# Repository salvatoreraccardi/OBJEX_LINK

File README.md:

# OBJEX Link 

**OBJEX Link website:** https://objex.link/

**OBJEX Link Docs:** https://docs.objex.link/

**email:** info@objex.link 

**OBJEX Link Shop:** https://www.tindie.com/stores/objex/

**Youtube:** <br />
Project introduction - **OBJEX Link** [watch the video](https://www.youtube.com/watch?v=X29LyX-1ozA)

Assembly and testing - **Protoboard&Socket_v2.0** [watch the video](https://www.youtube.com/watch?v=N7MFNUX0_PA)

Assembly and testing - **OBJEX Link v1.6-C3:** [watch the video](https://www.youtube.com/watch?v=o9e5-9o4egI)

Assembly and testing - **OBJEX Link v1.6:** [watch the video](https://www.youtube.com/watch?v=haHsvLIlmms)

Assembly and testing - **OBJEX Link v1.5:** [watch the video](https://www.youtube.com/watch?v=wx3dR2j1C28)

Assembly and testing - **OBJEX Link v1.0:** [watch the video](https://www.youtube.com/watch?v=_4CofqktS38)

## What is OBJEX Link?
OBJEX Link is a modular IoT board. It is designed to develop **IoT devices** that are **easy to repair** and **recycle**. OBJEX Link is designed to meet a wide range of uses: **Smart Home & Cities, IIOT, Everyday things & Wearables, Predictive Maintenance, Agriculture Automation.**

OBJEX Link can also be used for **rapid prototyping, and developing research and robotics projects, with the right module you can extend the possible uses of the board.**

The compact form factor and board design ensure easy use and maintenance of the board. The architecture of OBJEX Link is composed of two parts, the first is the mainboard (OBJEX Link) and the second is the module allows for easy customization and interfacing with hardware compared to other IoT boards.

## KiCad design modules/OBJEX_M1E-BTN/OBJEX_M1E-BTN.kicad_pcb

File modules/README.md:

# OBJEX Modules
Modules are an essential element of OBJEX Link. In fact, they are the modules that allow OBJEX Link to detect the temperature, control an motor etc - *(like Arduino shields but smaller and more compact)*.

**Here are some features/components you can add with modules:**
- Sensors
- Relay 
- Motor driver(Stepper Motor, DC, LRA, ERM).
- OLED Display
- Convert slimstack connectors to larger connectors (type 2.54mm pitch connectors).
- A specific circuit (such as LoRa Module, PSRAM, PWM controller, etc).

## Types of modules
There are several form formats to ensure maximum customization.

| Type | Description     | Size    | PCB thickness | Connector | Connector Type | 3V3 | 5V | A |
|------|-----------------|---------|---------------|-----------|----------------|-----|----|---|
| M0   | Standard Module | 10x20mm | 0.8mm         | 2         |  BM28B0              |  ✓   |  ✓  | 5 |
| M1   | Standard Module | 20x20mm | 0.8mm         | 4         |  BM28B0              |  ✓   |  ✓  | 5 |
| M1E   | With I2C EEPROM | 20x20mm | 0.8mm         | 4         |  BM28B0              |  ✓   |  ✓  | 5 |

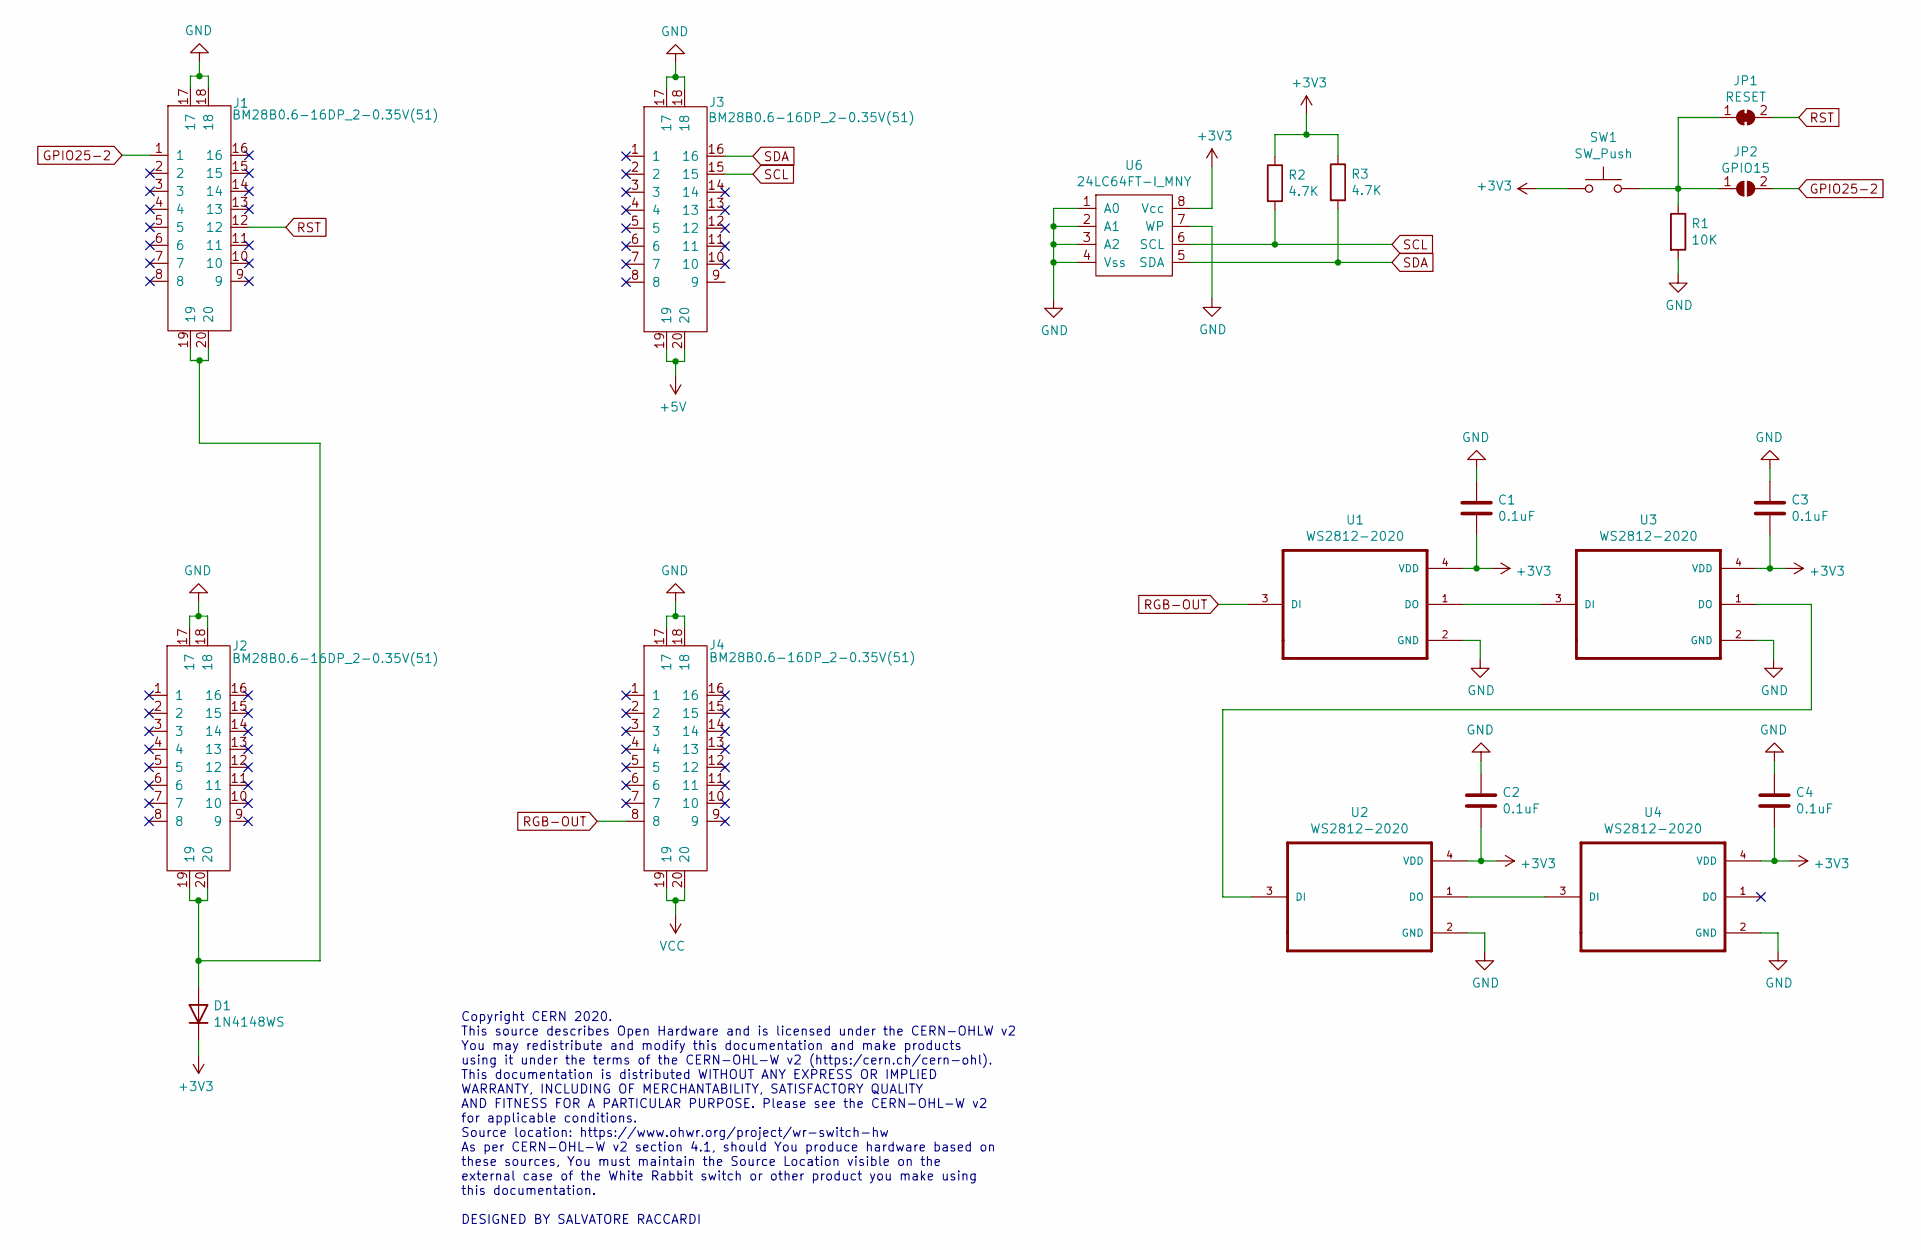
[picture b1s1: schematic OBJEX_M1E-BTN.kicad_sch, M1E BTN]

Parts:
C1, C2, C3, C4: 0.1uF; C_0402_1005Metric
D1: 1N4148WS; D_SOD-323
J1, J2, J3, J4: BM28B0.6-16DP_2-0.35V(51); BM28B0.6-16DP-2-0.35V(51)
JP1: RESET; SolderJumper-2_P1.3mm_Bridged_Pad1.0x1.5mm
JP2: GPIO15; SolderJumper-2_P1.3mm_Open_Pad1.0x1.5mm
R1: 10K; R_0402_1005Metric
R2, R3: 4.7K; R_0402_1005Metric
SW1: SW_Push; SW_Push_1P1T_NO_CK_PTS125Sx43PSMTR
U1, U2, U3, U4: WS2812-2020; LED_WS2812-2020
U6: 24LC64FT-I_MNY; SON50P200X300X80-8N

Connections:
+3V3: C1.2, C2.2, C3.2, C4.2, D1.1 (K), R2.1, R3.1, SW1.1, U1.4 (VDD), U2.4 (VDD), U3.4 (VDD), U4.4 (VDD), U6.8 (Vcc)
+5V: J3.19, J3.20
GND: C1.1, C2.1, C3.1, C4.1, J1.17, J1.18, J2.17, J2.18, J3.17, J3.18, J4.17, J4.18, R1.2, U1.2 (GND), U2.2 (GND), U3.2 (GND), U4.2 (GND), U6.1 (A0), U6.2 (A1), U6.3 (A2), U6.4 (Vss), U6.7 (WP)
GPIO25-2: J1.1, JP2.2 (B); also elsewhere on the board
unnamed: D1.2 (A), J1.19, J1.20, J2.19, J2.20
unnamed 64: JP1.1 (A), JP2.1 (A), R1.1, SW1.2; also elsewhere on the board
unnamed: U1.1 (DO), U3.3 (DI)
unnamed: U2.1 (DO), U4.3 (DI)
unnamed: U2.3 (DI), U3.1 (DO)
RGB-OUT: J4.8, U1.3 (DI)
RST: J1.12, JP1.2 (B); also elsewhere on the board
SCL: J3.15, R2.2, U6.6 (SCL)
SDA: J3.16, R3.2, U6.5 (SDA)
VCC: J4.19, J4.20

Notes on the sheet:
Copyright CERN 2020. This source describes Open Hardware and is licensed under the CERN-OHLW v2 You may redistribute and modify this documentation and make products using it under the terms of the CERN-OHL-W v2 (https:/cern.ch/cern-ohl). This documentation is distributed WITHOUT ANY EXPRESS OR IMPL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

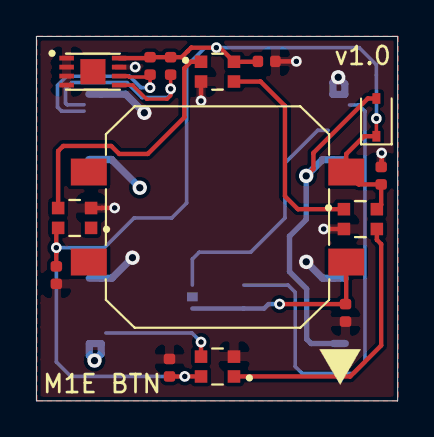
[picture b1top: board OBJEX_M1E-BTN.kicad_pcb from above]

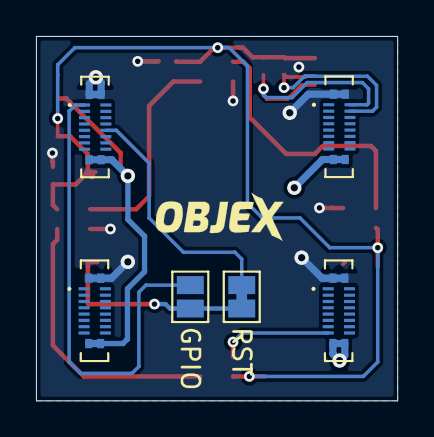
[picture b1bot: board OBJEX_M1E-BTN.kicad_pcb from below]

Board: 2 copper layers, 20.1 x 20.2 mm, 20 parts (6 on the bottom side), 14 nets.

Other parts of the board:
GPIO: GPIO15; SolderJumper-2_P1.3mm_Open_Pad1.0x1.5mm
RST: RESET; SolderJumper-2_P1.3mm_Bridged_Pad1.0x1.5mm

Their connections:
GPIO25-2: GPIO.2; also elsewhere on the board
unnamed 64: GPIO.1, RST.1; also elsewhere on the board
RST: RST.2; also elsewhere on the board

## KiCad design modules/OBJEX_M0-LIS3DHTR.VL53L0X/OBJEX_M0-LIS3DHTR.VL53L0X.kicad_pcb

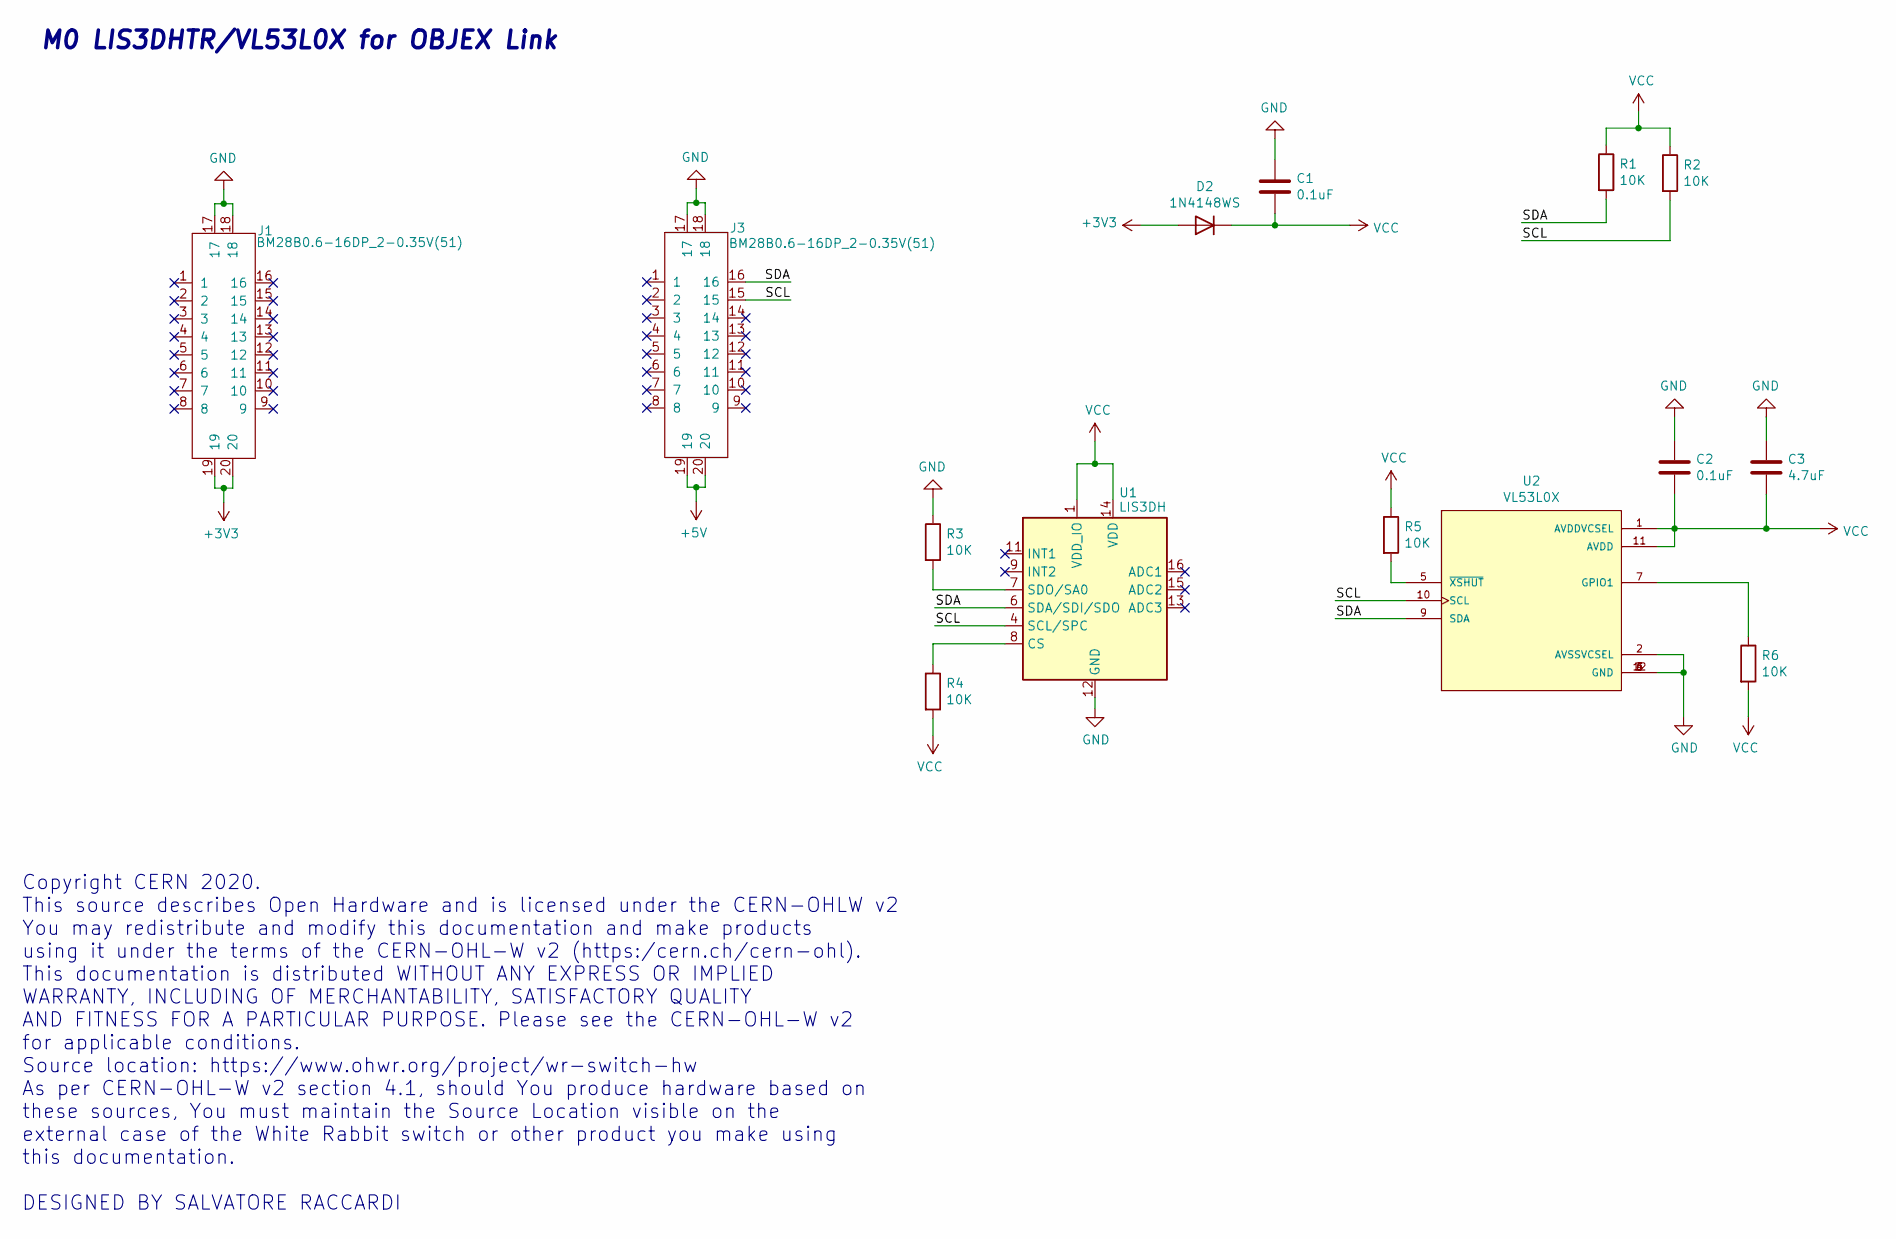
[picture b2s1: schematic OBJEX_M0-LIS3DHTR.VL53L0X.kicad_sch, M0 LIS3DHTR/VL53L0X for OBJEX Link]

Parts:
C1, C2: 0.1uF; C_0402_1005Metric
C3: 4.7uF; C_0402_1005Metric
D2: 1N4148WS; D_SOD-323
J1, J3: BM28B0.6-16DP_2-0.35V(51); BM28B0.6-16DP-2-0.35V(51)
R1, R2, R3, R4, R5, R6: 10K; R_0402_1005Metric
U1: LIS3DH; LGA-16_3x3mm_P0.5mm_LayoutBorder3x5y
U2: VL53L0X; SENSOR_VL53L0X; PART_REV 1.0

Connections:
+3V3: D2.2 (A), J1.19, J1.20
+5V: J3.19, J3.20
/SCL: J3.15, R2.2, U1.4 (SCL/SPC), U2.10 (SCL)
/SDA: J3.16, R1.2, U1.6 (SDA/SDI/SDO), U2.9 (SDA)
GND: C1.1, C2.1, C3.1, J1.17, J1.18, J3.17, J3.18, R3.1, U1.5 (GND), U1.10 (GND), U1.12 (GND), U2.2 (AVSSVCSEL), U2.3 (GND), U2.4 (GND), U2.6 (GND), U2.12 (GND)
unnamed: R3.2, U1.7 (SDO/SA0)
unnamed: R4.1, U1.8 (CS)
unnamed: R5.2, U2.5 (~XSHUT)
unnamed: R6.1, U2.7 (GPIO1)
VCC: C1.2, C2.2, C3.2, D2.1 (K), R1.1, R2.1, R4.2, R5.1, R6.2, U1.1 (VDD_IO), U1.14 (VDD), U2.1 (AVDDVCSEL), U2.11 (AVDD)

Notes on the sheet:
Copyright CERN 2020. This source describes Open Hardware and is licensed under the CERN-OHLW v2 You may redistribute and modify this documentation and make products using it under the terms of the CERN-OHL-W v2 (https:/cern.ch/cern-ohl). This documentation is distributed WITHOUT ANY EXPRESS OR IMPL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
M0 LIS3DHTR/VL53L0X for OBJEX Link

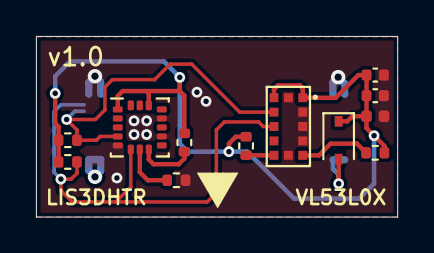
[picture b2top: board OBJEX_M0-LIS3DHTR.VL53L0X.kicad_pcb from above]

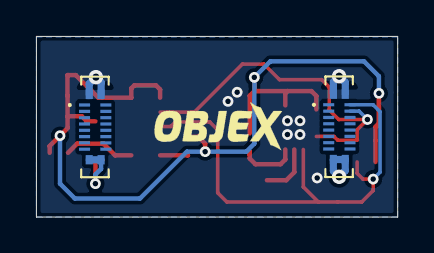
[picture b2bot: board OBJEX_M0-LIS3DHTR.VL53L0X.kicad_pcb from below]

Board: 2 copper layers, 20.1 x 10.0 mm, 14 parts (2 on the bottom side), 10 nets.

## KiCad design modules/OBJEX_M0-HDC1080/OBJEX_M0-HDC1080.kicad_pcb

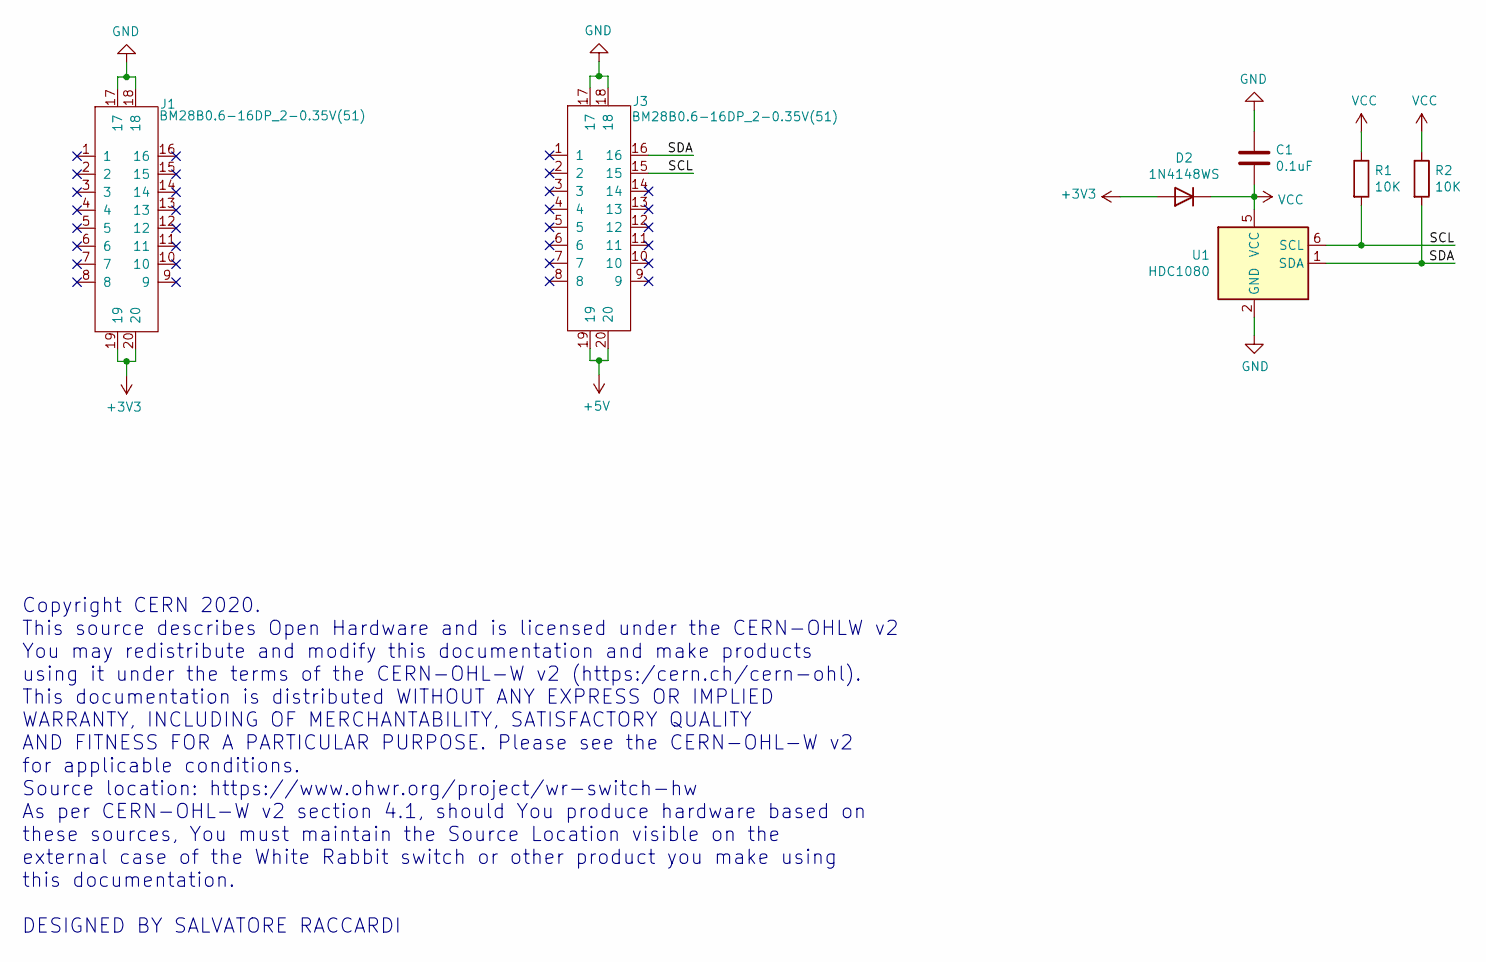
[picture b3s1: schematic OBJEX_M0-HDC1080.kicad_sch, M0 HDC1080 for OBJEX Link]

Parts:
C1: 0.1uF; C_0402_1005Metric
D2: 1N4148WS; D_SOD-323
J1, J3: BM28B0.6-16DP_2-0.35V(51); BM28B0.6-16DP-2-0.35V(51)
R1, R2: 10K; R_0603_1608Metric
U1: HDC1080; Texas_PWSON-N6

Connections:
+3V3: D2.2 (A), J1.19, J1.20
+5V: J3.19, J3.20
/SCL: J3.15, R1.2, U1.6 (SCL)
/SDA: J3.16, R2.2, U1.1 (SDA)
GND: C1.1, J1.17, J1.18, J3.17, J3.18, U1.2 (GND)
VCC: C1.2, D2.1 (K), R1.1, R2.1, U1.5 (VCC)

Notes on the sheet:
Copyright CERN 2020. This source describes Open Hardware and is licensed under the CERN-OHLW v2 You may redistribute and modify this documentation and make products using it under the terms of the CERN-OHL-W v2 (https:/cern.ch/cern-ohl). This documentation is distributed WITHOUT ANY EXPRESS OR IMPL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

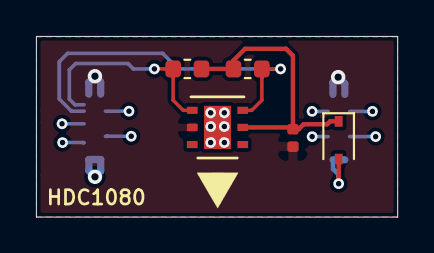
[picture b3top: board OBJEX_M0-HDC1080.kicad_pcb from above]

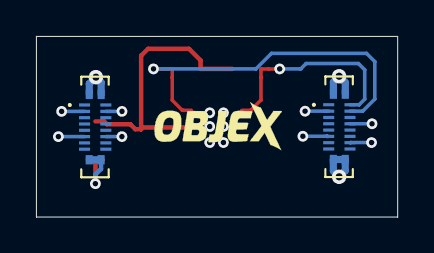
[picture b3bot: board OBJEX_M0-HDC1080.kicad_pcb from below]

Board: 2 copper layers, 20.1 x 10.0 mm, 7 parts (2 on the bottom side), 6 nets.

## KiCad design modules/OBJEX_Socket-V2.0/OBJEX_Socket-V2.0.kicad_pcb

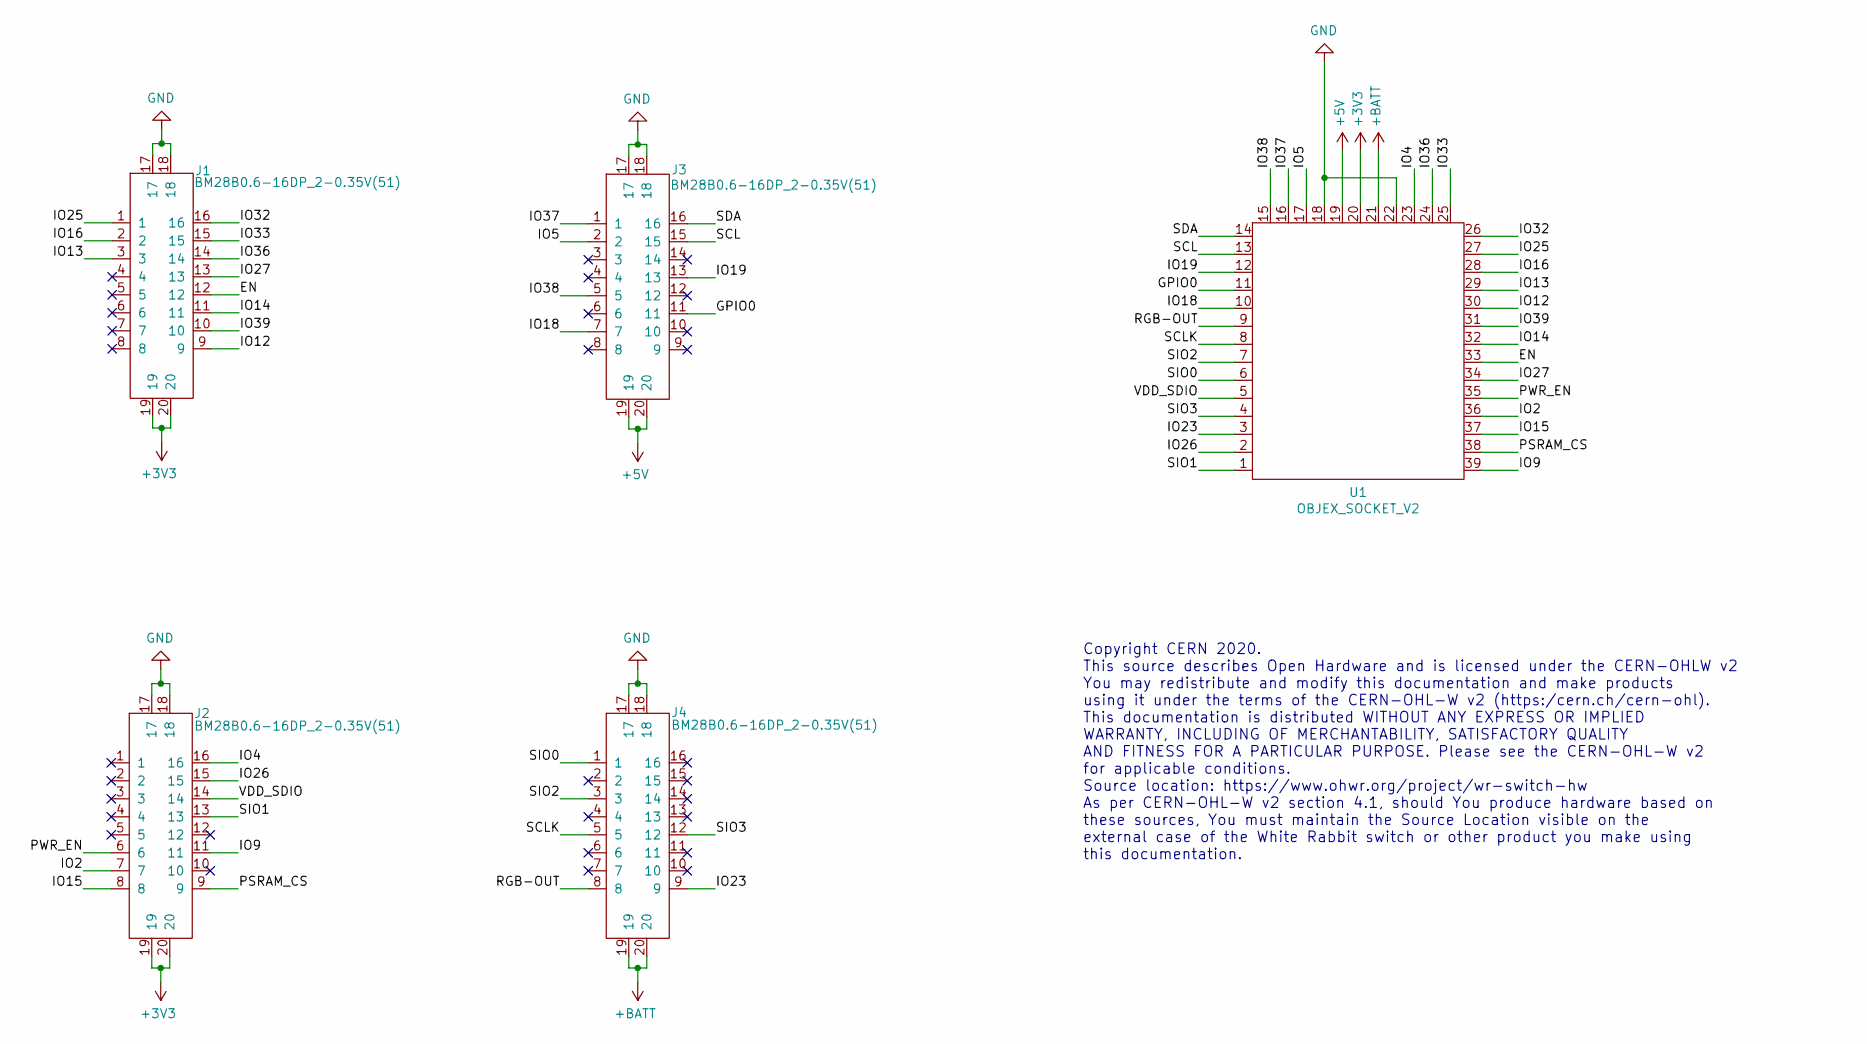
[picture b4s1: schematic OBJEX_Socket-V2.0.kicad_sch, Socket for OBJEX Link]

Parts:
J1, J2, J3, J4: BM28B0.6-16DP_2-0.35V(51); BM28B0.6-16DP-2-0.35V(51)
U1: OBJEX_SOCKET_V2; OBJEX_Link-Castellated

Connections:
+3V3: J1.19, J1.20, J2.19, J2.20, U1.20
+5V: J3.19, J3.20, U1.19
+BATT: J4.19, J4.20, U1.21
/EN: J1.12, U1.33
/GPIO0: J3.11, U1.11
/IO2: J2.7, U1.36
/IO4: J2.16, U1.23
/IO5: J3.2, U1.17
/IO9: J2.11, U1.39
/IO12: J1.9, U1.30
/IO13: J1.3, U1.29
/IO14: J1.11, U1.32
/IO15: J2.8, U1.37
/IO16: J1.2, U1.28
/IO18: J3.7, U1.10
/IO19: J3.13, U1.12
/IO23: J4.9, U1.3
/IO25: J1.1, U1.27
/IO26: J2.15, U1.2
/IO27: J1.13, U1.34
/IO32: J1.16, U1.26
/IO33: J1.15, U1.25
/IO36: J1.14, U1.24
/IO37: J3.1, U1.16
/IO38: J3.5, U1.15
/IO39: J1.10, U1.31
/PSRAM_CS: J2.9, U1.38
/PWR_EN: J2.6, U1.35
/RGB-OUT: J4.8, U1.9
/SCL: J3.15, U1.13
/SCLK: J4.5, U1.8
/SDA: J3.16, U1.14
/SIO0: J4.1, U1.6
/SIO1: J2.13, U1.1
/SIO2: J4.3, U1.7
/SIO3: J4.12, U1.4
/VDD_SDIO: J2.14, U1.5
GND: J1.17, J1.18, J2.17, J2.18, J3.17, J3.18, J4.17, J4.18, U1.18, U1.22

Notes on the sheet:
Copyright CERN 2020. This source describes Open Hardware and is licensed under the CERN-OHLW v2 You may redistribute and modify this documentation and make products using it under the terms of the CERN-OHL-W v2 (https:/cern.ch/cern-ohl). This documentation is distributed WITHOUT ANY EXPRESS OR IMPL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

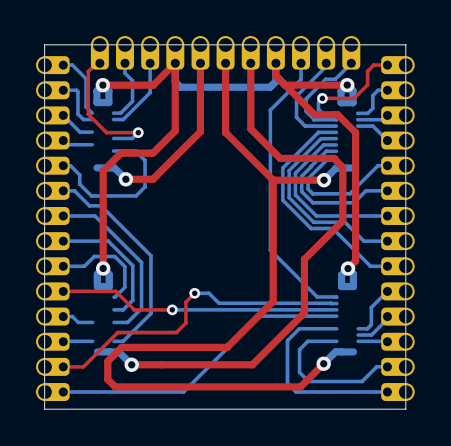
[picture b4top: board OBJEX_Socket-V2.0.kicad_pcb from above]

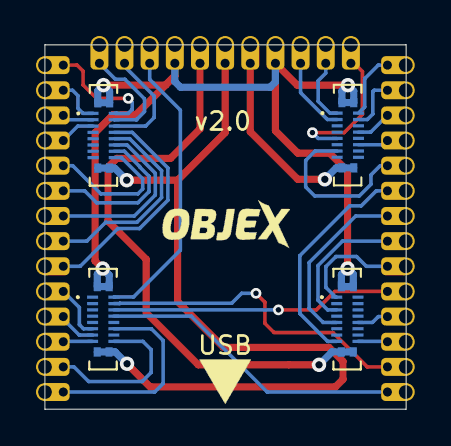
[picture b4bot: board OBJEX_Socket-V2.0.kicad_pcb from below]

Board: 2 copper layers, 20.1 x 20.2 mm, 5 parts (4 on the bottom side), 38 nets.

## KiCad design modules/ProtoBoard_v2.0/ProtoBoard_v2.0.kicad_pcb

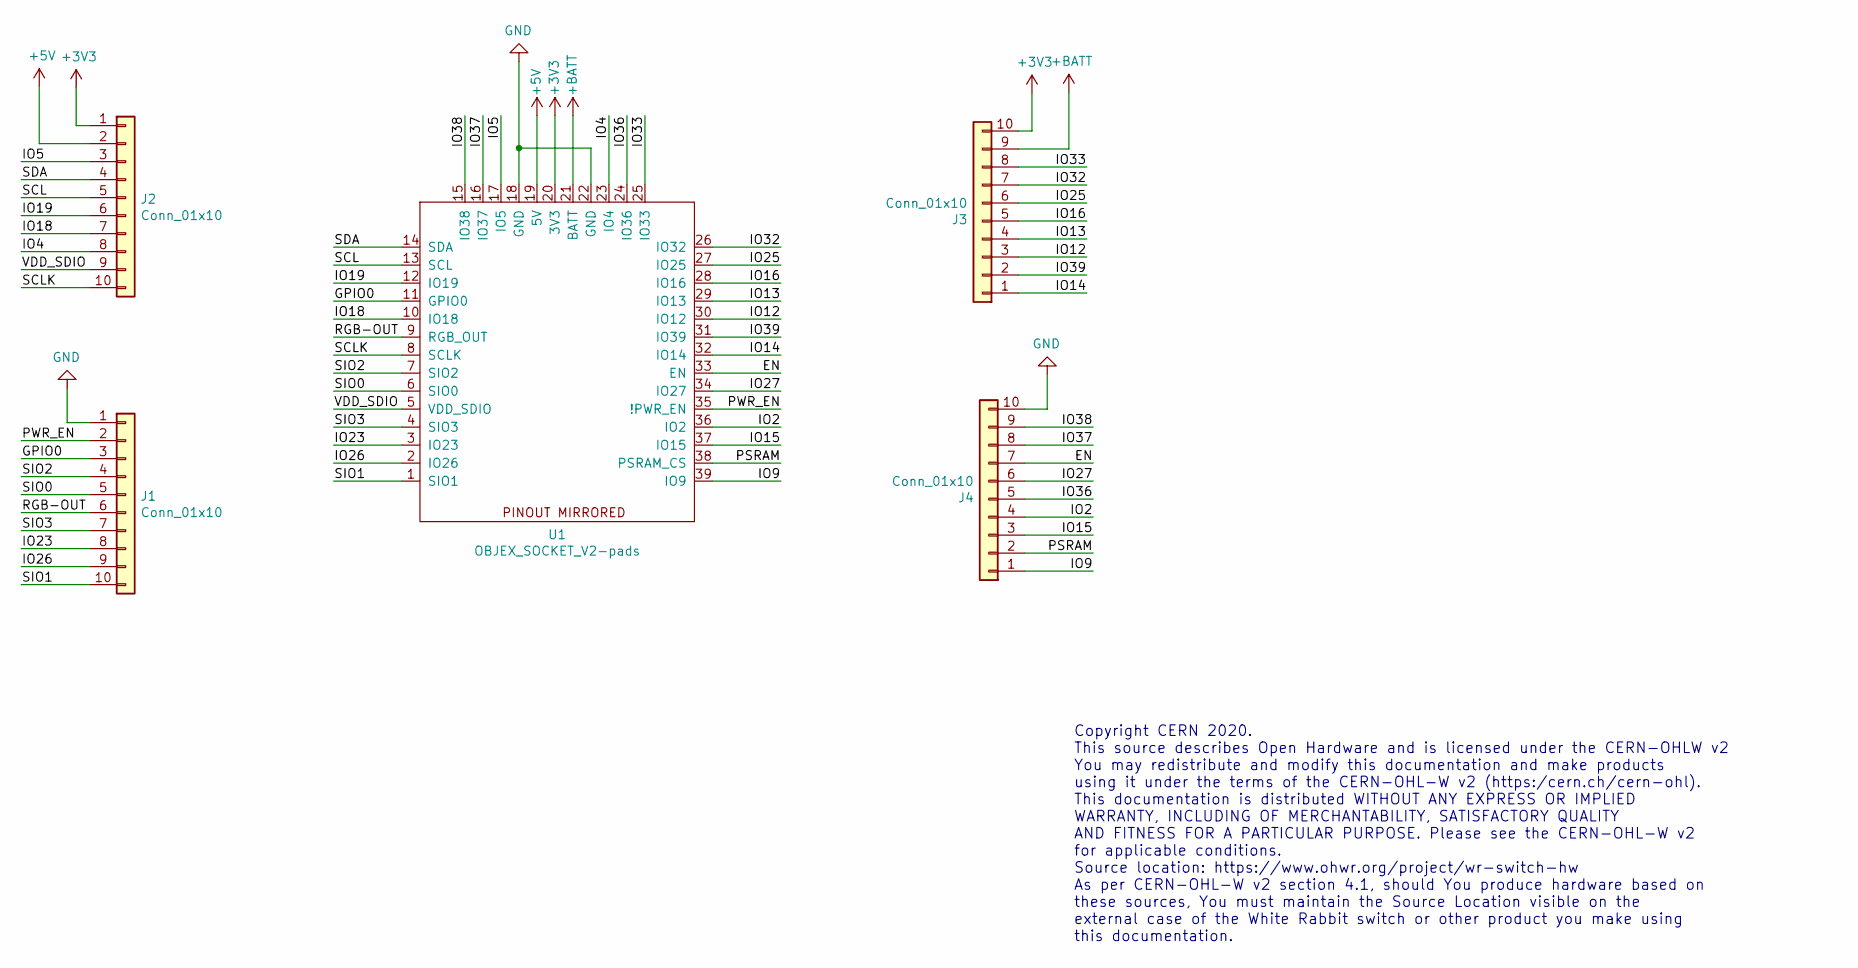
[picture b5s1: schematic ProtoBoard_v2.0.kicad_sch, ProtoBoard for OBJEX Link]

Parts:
J1, J2, J3, J4: Conn_01x10; PinHeader_1x10_P2.54mm_Vertical
U1: OBJEX_SOCKET_V2-pads; OBJEX_Link-Pads

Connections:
+3V3: J2.1, J3.10, U1.20 (3V3)
+5V: J2.2, U1.19 (5V)
+BATT: J3.9, U1.21 (BATT)
/EN: J4.7, U1.33 (EN)
/GPIO0: J1.3, U1.11 (GPIO0)
/IO2: J4.4, U1.36 (IO2)
/IO4: J2.8, U1.23 (IO4)
/IO5: J2.3, U1.17 (IO5)
/IO9: J4.1, U1.39 (IO9)
/IO12: J3.3, U1.30 (IO12)
/IO13: J3.4, U1.29 (IO13)
/IO14: J3.1, U1.32 (IO14)
/IO15: J4.3, U1.37 (IO15)
/IO16: J3.5, U1.28 (IO16)
/IO18: J2.7, U1.10 (IO18)
/IO19: J2.6, U1.12 (IO19)
/IO23: J1.8, U1.3 (IO23)
/IO25: J3.6, U1.27 (IO25)
/IO26: J1.9, U1.2 (IO26)
/IO27: J4.6, U1.34 (IO27)
/IO32: J3.7, U1.26 (IO32)
/IO33: J3.8, U1.25 (IO33)
/IO36: J4.5, U1.24 (IO36)
/IO37: J4.8, U1.16 (IO37)
/IO38: J4.9, U1.15 (IO38)
/IO39: J3.2, U1.31 (IO39)
/PSRAM: J4.2, U1.38 (PSRAM_CS)
/PWR_EN: J1.2, U1.35 (!PWR_EN)
/RGB-OUT: J1.6, U1.9 (RGB_OUT)
/SCL: J2.5, U1.13 (SCL)
/SCLK: J2.10, U1.8 (SCLK)
/SDA: J2.4, U1.14 (SDA)
/SIO0: J1.5, U1.6 (SIO0)
/SIO1: J1.10, U1.1 (SIO1)
/SIO2: J1.4, U1.7 (SIO2)
/SIO3: J1.7, U1.4 (SIO3~)
/VDD_SDIO: J2.9, U1.5 (VDD_SDIO)
GND: J1.1, J4.10, U1.18 (GND), U1.22 (GND)

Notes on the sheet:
Copyright CERN 2020. This source describes Open Hardware and is licensed under the CERN-OHLW v2 You may redistribute and modify this documentation and make products using it under the terms of the CERN-OHL-W v2 (https:/cern.ch/cern-ohl). This documentation is distributed WITHOUT ANY EXPRESS OR IMPL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

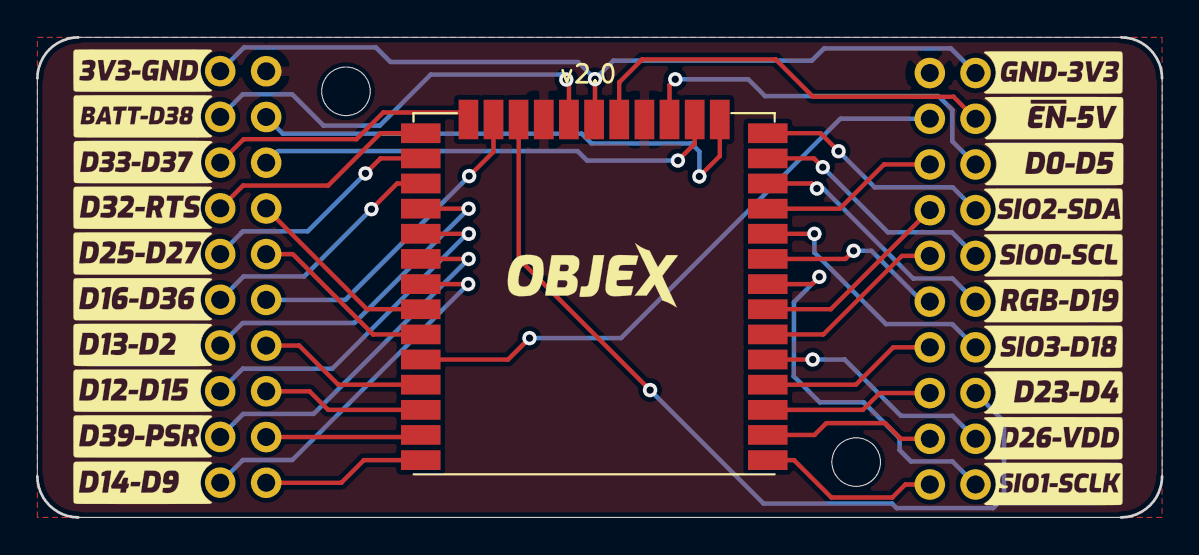
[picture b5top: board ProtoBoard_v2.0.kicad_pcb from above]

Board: 2 copper layers, 62.5 x 26.7 mm, 5 parts (0 on the bottom side), 38 nets.

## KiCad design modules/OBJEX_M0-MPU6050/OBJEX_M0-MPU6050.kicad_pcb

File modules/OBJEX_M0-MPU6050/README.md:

## COPYRIGHT
Copyright CERN 2020.

This source describes Open Hardware and is licensed under the CERN-OHLW v2

You may redistribute and modify this documentation and make products
using it under the terms of the CERN-OHL-W v2 (https:/cern.ch/cern-ohl).
This documentation is distributed WITHOUT ANY EXPRESS OR IMPLIED
WARRANTY, INCLUDING OF MERCHANTABILITY, SATISFACTORY QUALITY
AND FITNESS FOR A PARTICULAR PURPOSE. Please see the CERN-OHL-W v2
for applicable conditions.

Source location: https://www.ohwr.org/project/wr-switch-hw

As per CERN-OHL-W v2 section 4.1, should You produce hardware based on
these sources, You must maintain the Source Location visible on the
external case of the White Rabbit switch or other product you make using
this documentation.

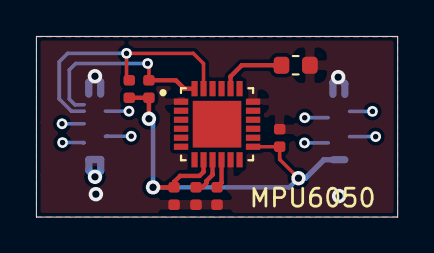
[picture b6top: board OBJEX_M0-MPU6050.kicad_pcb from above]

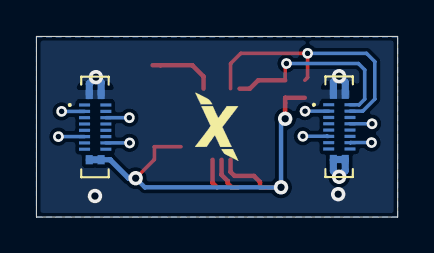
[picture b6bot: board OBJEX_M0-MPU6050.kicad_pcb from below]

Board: 2 copper layers, 20.1 x 10.0 mm, 10 parts (2 on the bottom side), 9 nets.

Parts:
C1: 2200pF; C_0603_1608Metric
C2, C4: 0.1uF; C_0402_1005Metric
C3: 0.01uF; C_0402_1005Metric
J1, J3: BM28B0.6-16DP_2-0.35V(51); BM28B0.6-16DP-2-0.35V(51)
R1, R2, R3: 4.7K; R_0402_1005Metric
U1: MPU6050; IC_MPU6050

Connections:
+3V3: C3.1, C4.1, J1.19, J1.20, R1.1, R2.1, U1.8, U1.13
+5V: J3.19, J3.20
/SCL: J3.15, R2.2, U1.23
/SDA: J3.16, R1.2, U1.24
GND: C1.2, C2.2, C3.2, C4.2, J1.17, J1.18, J3.17, J3.18, R3.1, U1.1, U1.11, U1.18
unnamed: C1.1, U1.20
unnamed: C2.1, U1.10
unnamed: R3.2, U1.9
unnamed: U1.19, U1.21

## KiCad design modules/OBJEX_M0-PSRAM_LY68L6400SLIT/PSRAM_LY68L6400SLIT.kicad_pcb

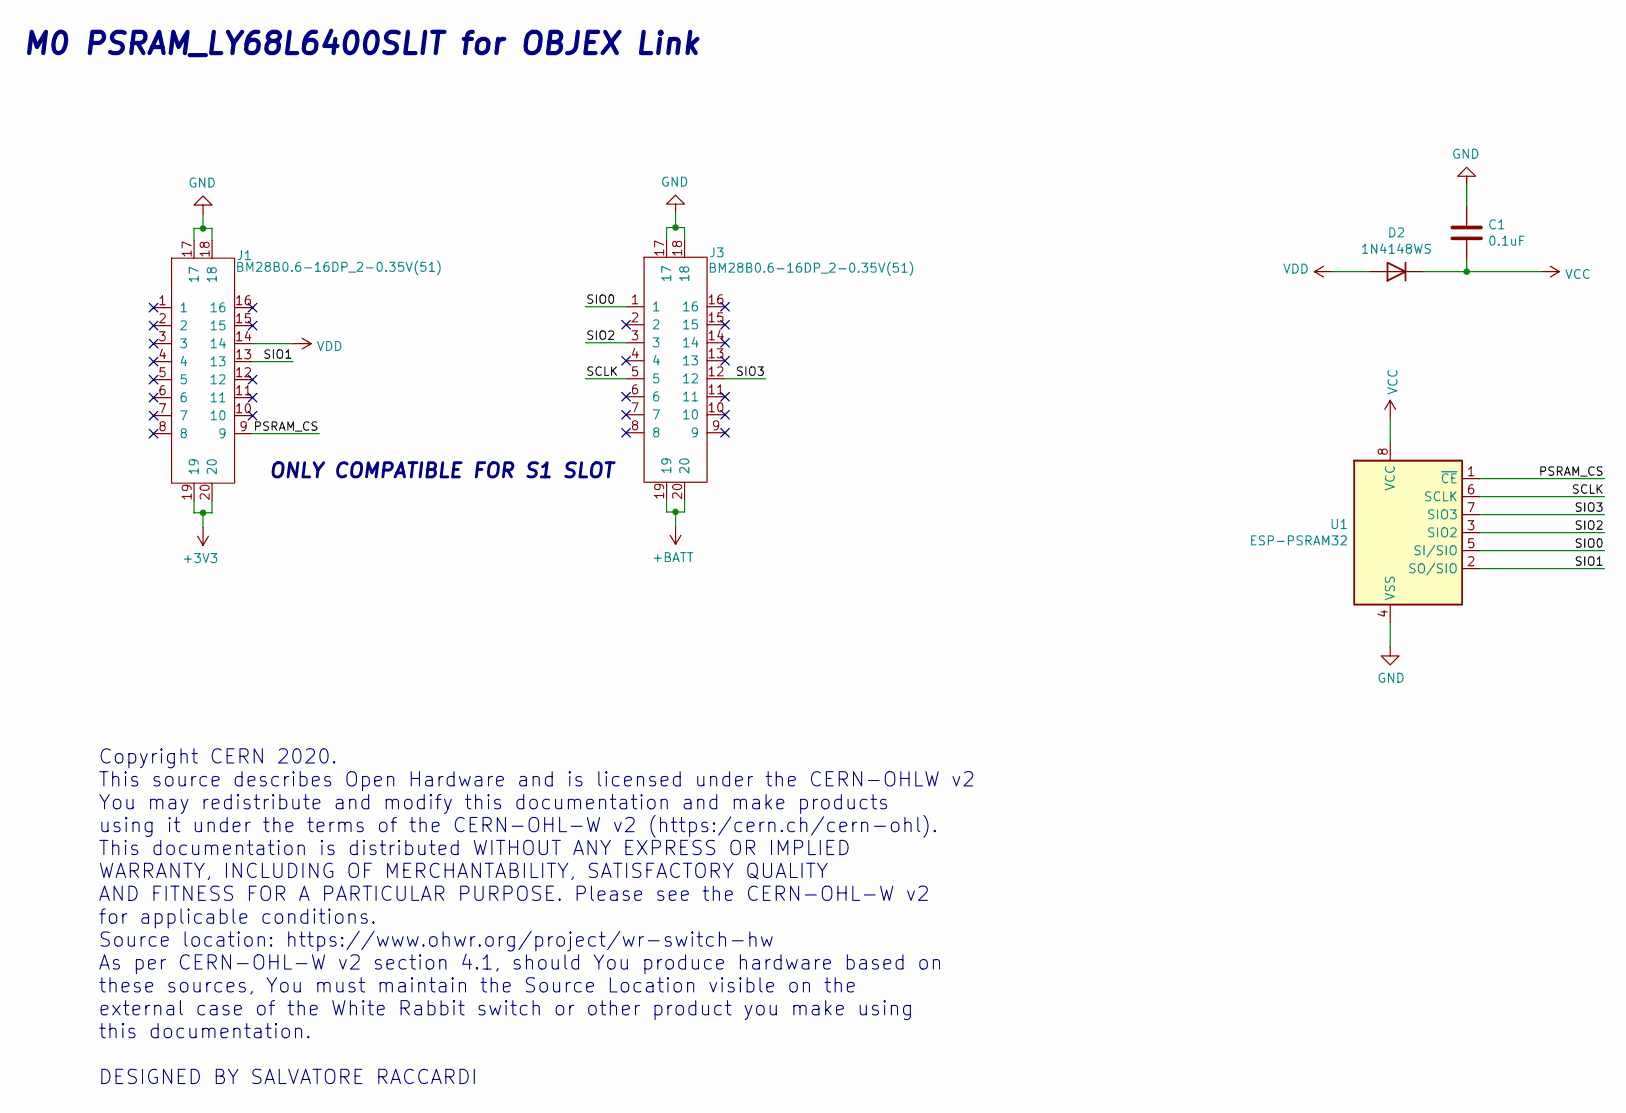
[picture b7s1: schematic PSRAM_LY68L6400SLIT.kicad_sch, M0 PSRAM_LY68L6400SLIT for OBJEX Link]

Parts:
C1: 0.1uF; C_0402_1005Metric
D2: 1N4148WS; D_SOD-323
J1, J3: BM28B0.6-16DP_2-0.35V(51); BM28B0.6-16DP-2-0.35V(51)
U1: ESP-PSRAM32; SOIC-8_3.9x4.9mm_P1.27mm

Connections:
+3V3: J1.19, J1.20
+BATT: J3.19, J3.20
/PSRAM_CS: J1.9, U1.1 (~CE)
/SCLK: J3.5, U1.6 (SCLK)
/SIO0: J3.1, U1.5 (SI/SIO)
/SIO1: J1.13, U1.2 (SO/SIO)
/SIO2: J3.3, U1.3 (SIO2)
/SIO3: J3.12, U1.7 (SIO3)
GND: C1.1, J1.17, J1.18, J3.17, J3.18, U1.4 (VSS)
VCC: C1.2, D2.1 (K), U1.8 (VCC)
VDD: D2.2 (A), J1.14

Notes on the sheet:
Copyright CERN 2020. This source describes Open Hardware and is licensed under the CERN-OHLW v2 You may redistribute and modify this documentation and make products using it under the terms of the CERN-OHL-W v2 (https:/cern.ch/cern-ohl). This documentation is distributed WITHOUT ANY EXPRESS OR IMPL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
ONLY COMPATIBLE FOR S1 SLOT
M0 PSRAM_LY68L6400SLIT for OBJEX Link

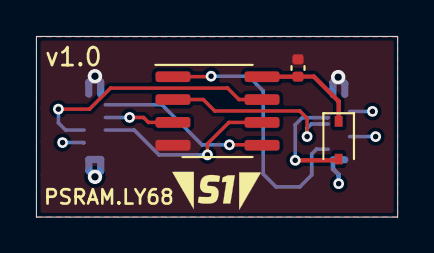
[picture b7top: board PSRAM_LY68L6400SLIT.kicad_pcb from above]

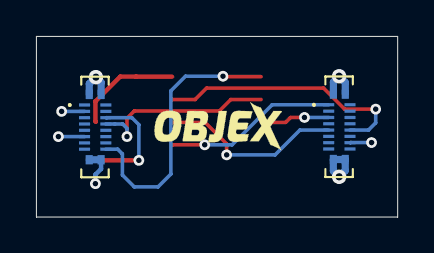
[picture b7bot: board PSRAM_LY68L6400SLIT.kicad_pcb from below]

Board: 2 copper layers, 20.1 x 10.0 mm, 5 parts (2 on the bottom side), 11 nets.

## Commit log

2021-03-27 dir update
2021-03-27 upload
2021-03-27 Create About
2021-03-27 Rename About to README
2021-04-03 beta1.0 3D Case
2021-04-03 move
2021-04-03 fade effect
2021-04-05 Create LICENSE
2021-04-09 footprint
2021-07-08 Create troubleshooting
2021-07-08 Rename troubleshooting to troubleshooting.md
2021-07-10 Add: png for wiki
2021-07-11 add: pinout
2021-07-11 add: pinout_2
2021-07-11 add: pinout_3
2021-07-11 add: blockdiagram_1
2021-07-13 add: QuickStart(.jpg)
2021-07-21 add: modules_img
2021-07-26 edit name png
2021-07-26 edit
2021-07-28 add copyright txt
2021-07-31 add: some photos
2021-08-03 add photos
2021-09-26 add new cover v2.1
2021-11-04 add: docs boards
2021-11-04 General update for new boards/modules
2021-11-18 add: all schematics
2021-11-18 FIX: schematics
2021-11-29 update docs
2021-12-10 Add: PSRAM Module v1.0
2021-12-15 add: LIS3DHTR-VL53L0X Module
2021-12-28 Add: OBJEX Link v1.7-C3 RISCV
2022-01-04 Add: M1E IoT BTN Module
2022-03-03 add: demo firmware
2022-03-14 add new board: OBJEX Link v1.6_RF
2022-04-04 Add: CAD file for Socket v2.0
